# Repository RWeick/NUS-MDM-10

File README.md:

# NUS-MDM-10
The kicad schematic and pcb layout of the NUS-MDM-10 Nintendo 64DD modem cartridge

PCB Thickness: 1.2 mm

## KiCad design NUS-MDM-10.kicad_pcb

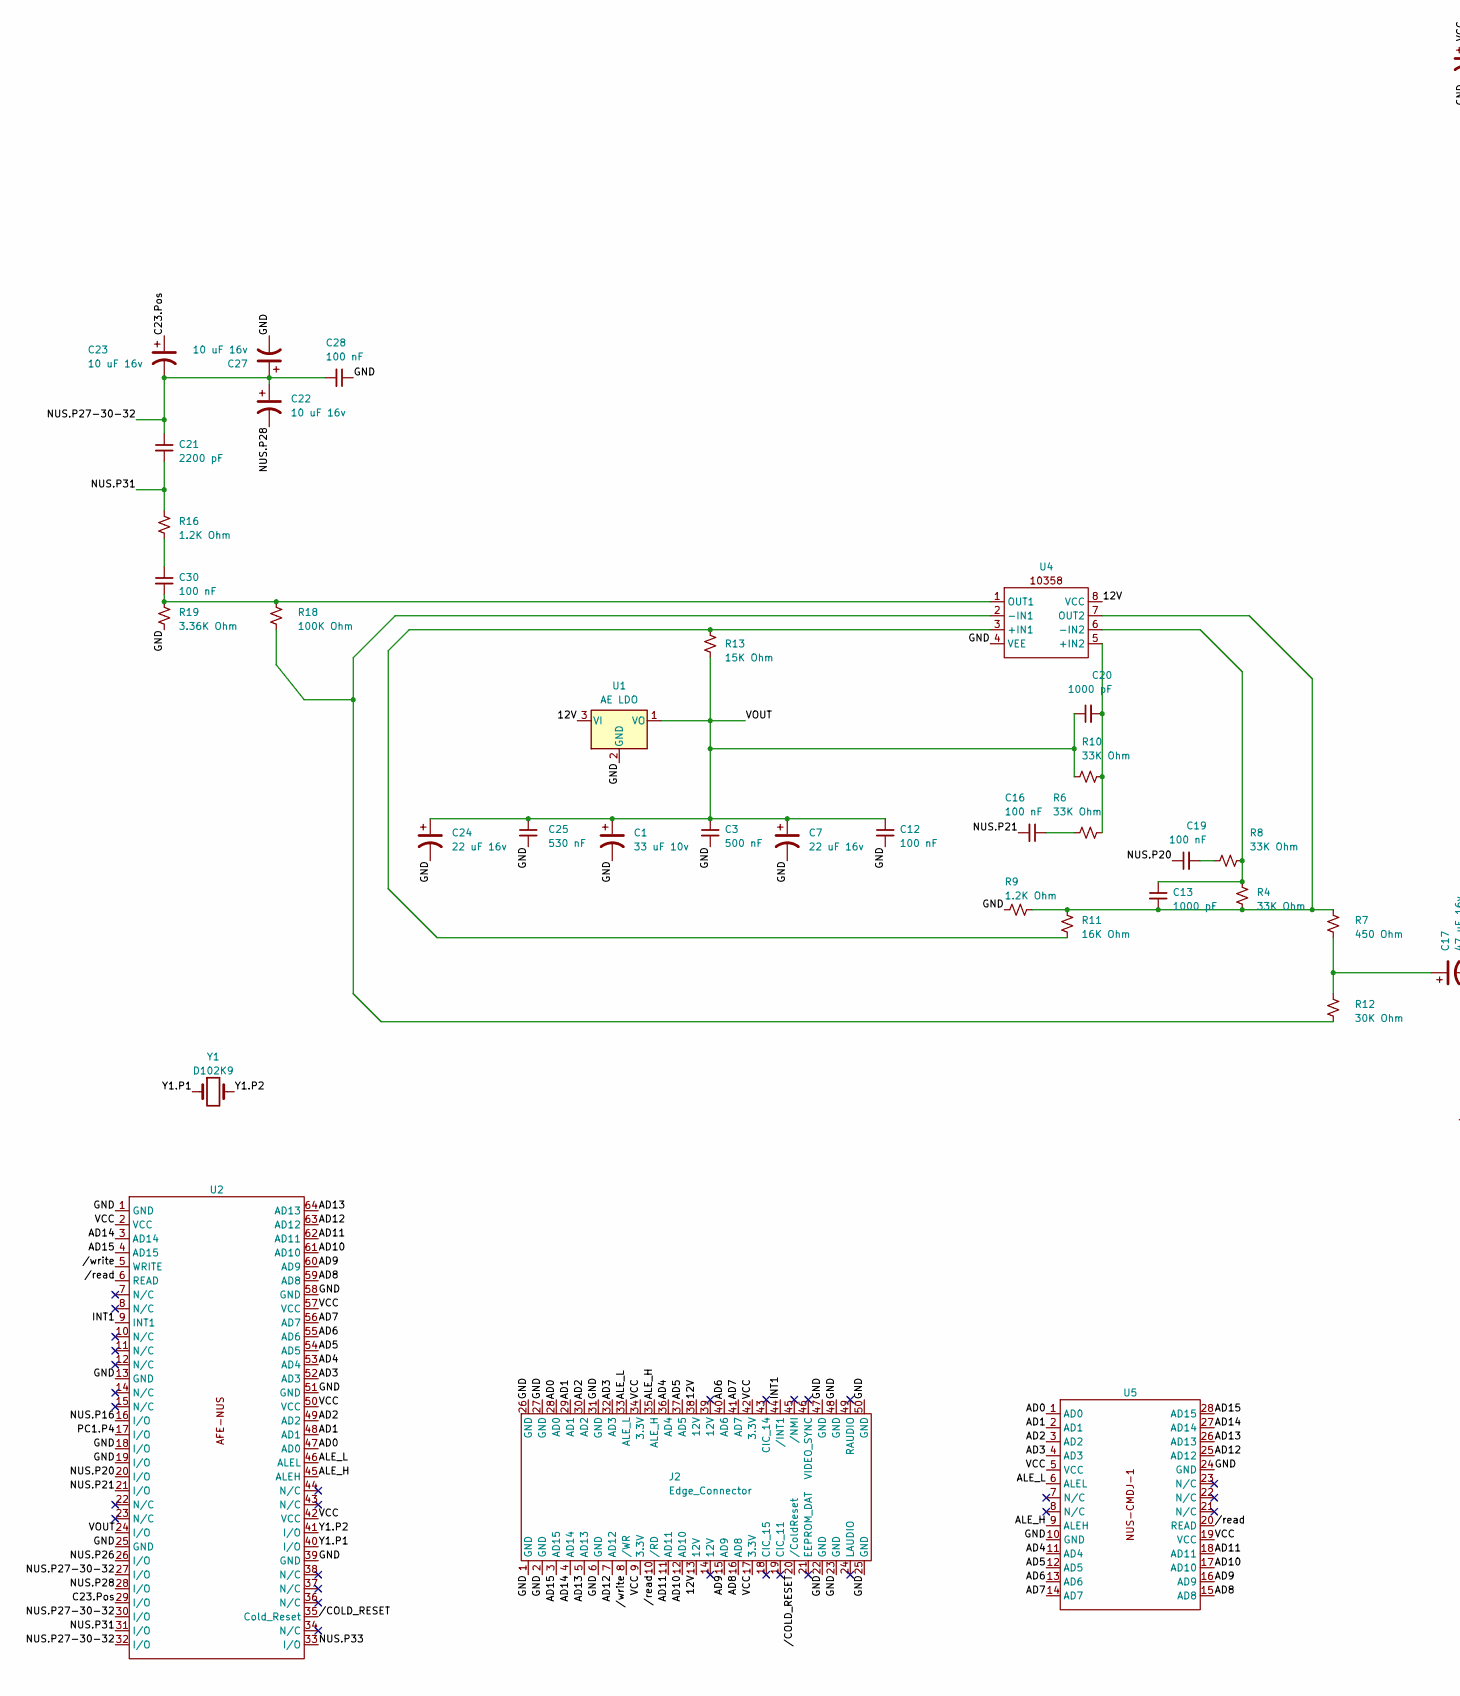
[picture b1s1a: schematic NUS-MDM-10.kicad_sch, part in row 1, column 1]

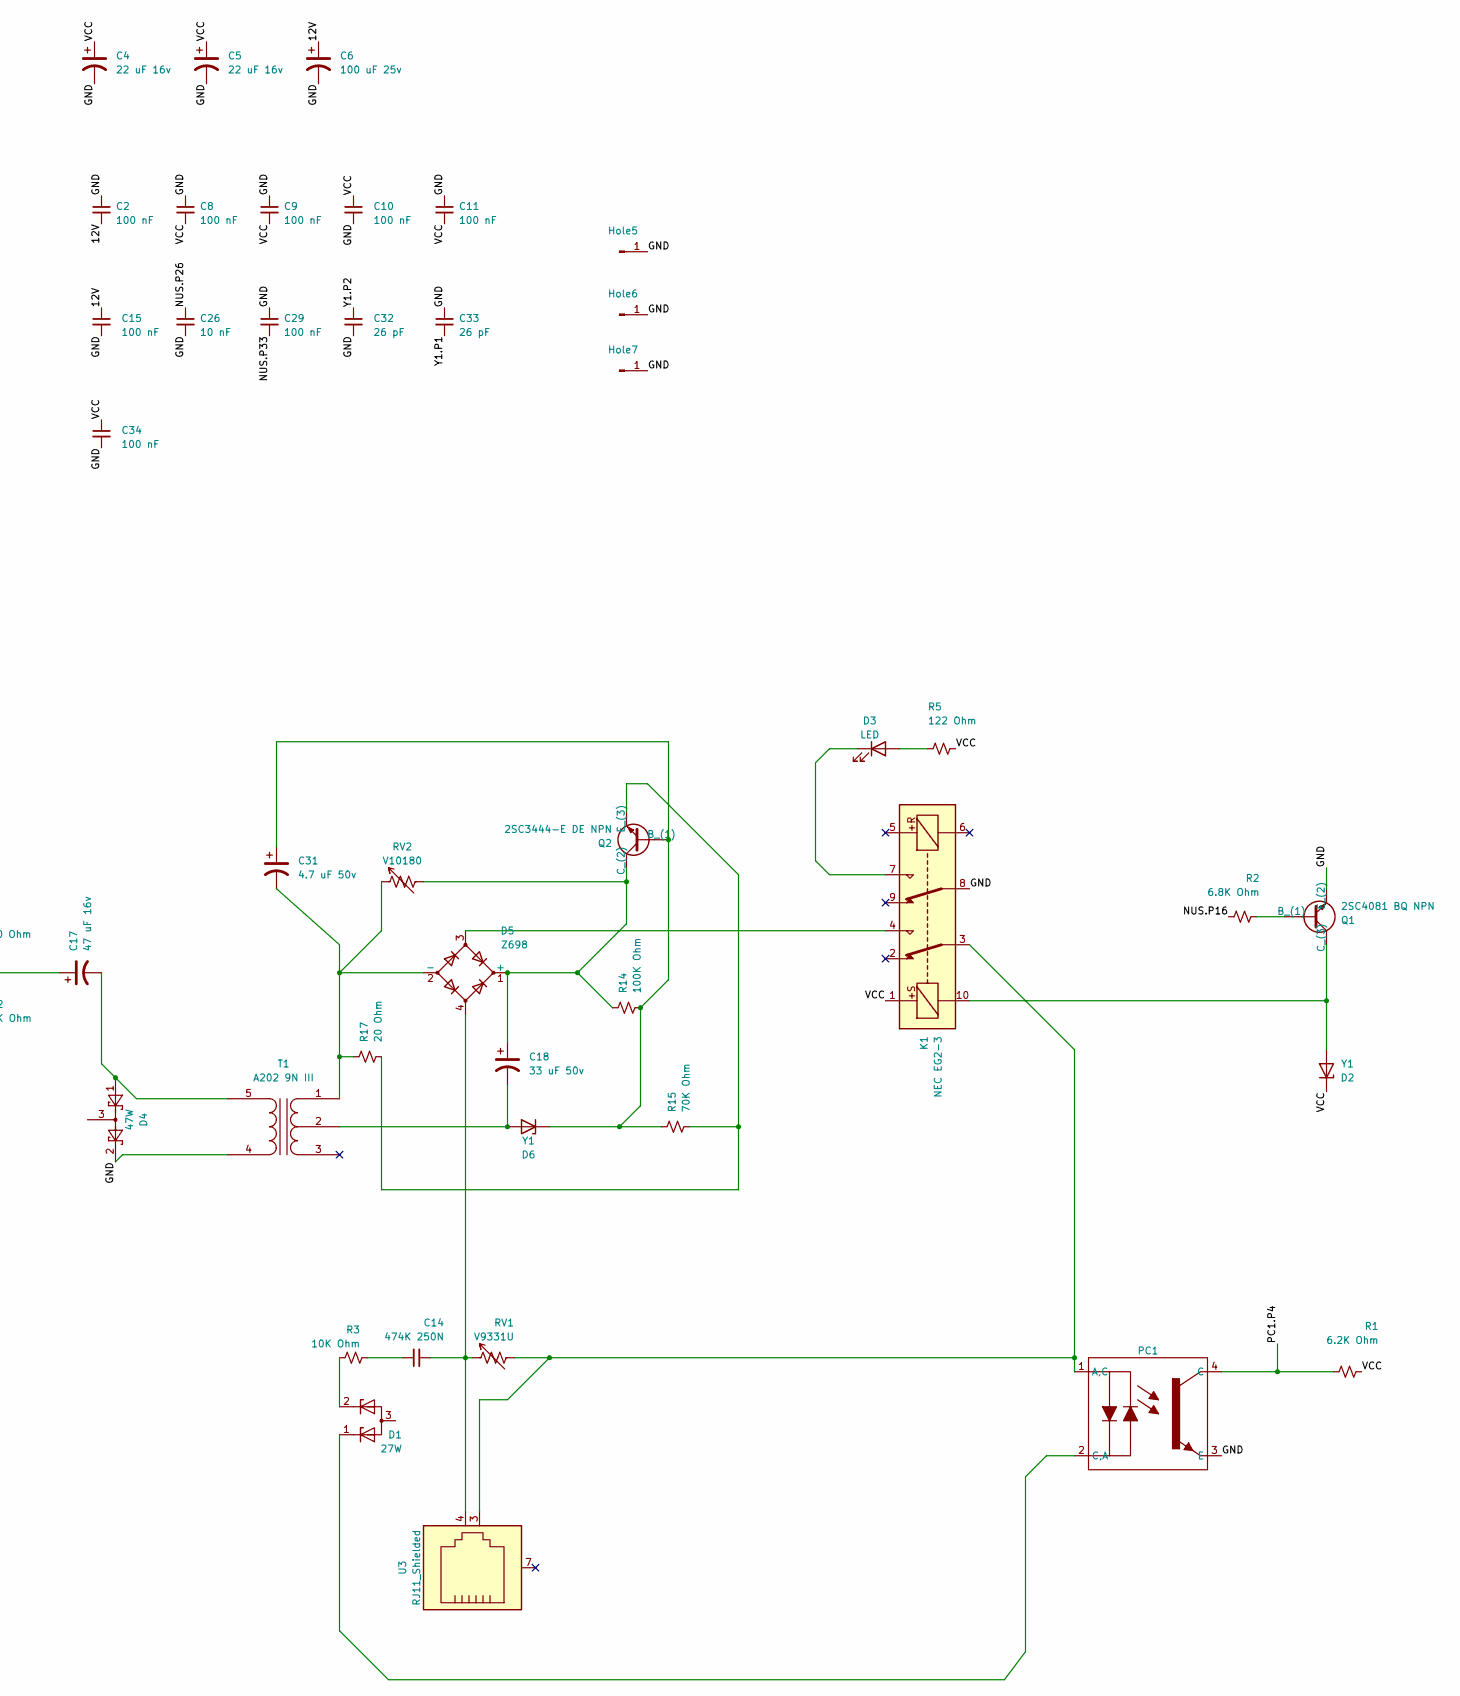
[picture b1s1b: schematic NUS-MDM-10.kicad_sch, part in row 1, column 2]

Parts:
C1: 33 uF 10v; C1
C2, C8, C9, C10, C11, C12, C15, C16, C19, C28, C29, C30, C34: 100 nF; SMD Cap Res
C3: 500 nF; SMD Cap Res
C4: 22 uF 16v; C4
C5: 22 uF 16v; C5
C6: 100 uF 25v; C6
C7: 22 uF 16v; C7
C13, C20: 1000 pF; SMD Cap Res
C14: 474K 250N; 474K Capacitor
C17: 47 uF 16v; C17
C18: 33 uF 50v; C18
C21: 2200 pF; SMD Cap Res
C22: 10 uF 16v; C22
C23: 10 uF 16v; C23
C24: 22 uF 16v; C24
C25: 530 nF; SMD Cap Res
C26: 10 nF; SMD Cap Res
C27: 10 uF 16v; C27
C31: 4.7 uF 50v; C31
C32, C33: 26 pF; SMD Cap Res
D1: 27W; D1
D2: Y1; D2
D3: LED
D4: 47W; D4
D5: Z698; 869Z
D6: Y1; D6
Hole5, Hole6, Hole7: Conn_01x01_Pin; Ground Panel Mounting Hole
J2: Edge_Connector; Cartridge Edge Connector
K1: NEC EG2-3
PC1: PC1
Q1: 2SC4081 BQ NPN; Q1
Q2: 2SC3444-E DE NPN; Q2
R1: 6.2K Ohm; SMD Cap Res
R2: 6.8K Ohm; SMD Cap Res
R3: 10K Ohm; SMD Cap Res
R4, R6, R8, R10: 33K Ohm; SMD Cap Res
R5: 122 Ohm; SMD Cap Res
R7: 450 Ohm; SMD Cap Res
R9, R16: 1.2K Ohm; SMD Cap Res
R11: 16K Ohm; SMD Cap Res
R12: 30K Ohm; SMD Cap Res
R13: 15K Ohm; SMD Cap Res
R14, R18: 100K Ohm; SMD Cap Res
R15: 70K Ohm; SMD Cap Res
R17: 20 Ohm; SMD Cap Res
R19: 3.36K Ohm; SMD Cap Res
RV1: V9331U
RV2: V10180
T1: A202 9N III; A202 Transformer
U1: AE LDO; U1
U2: AFE-NUS
U3: RJ11_Shielded; RJ11
U4: 10358
U5: NUS-CMDJ-1
Y1: D102K9

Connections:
/12V: C2.2, C6.1, C15.1, U1.3 (VI), U4.8 (VCC); also elsewhere on the board
/AD0: U2.47 (AD0), U5.1 (AD0); also elsewhere on the board
/AD1: U2.48 (AD1), U5.2 (AD1); also elsewhere on the board
/AD2: U2.49 (AD2), U5.3 (AD2); also elsewhere on the board
/AD3: U2.52 (AD3), U5.4 (AD3); also elsewhere on the board
/AD4: U2.53 (AD4), U5.11 (AD4); also elsewhere on the board
/AD5: U2.54 (AD5), U5.12 (AD5); also elsewhere on the board
/AD6: U2.55 (AD6), U5.13 (AD6); also elsewhere on the board
/AD7: U2.56 (AD7), U5.14 (AD7); also elsewhere on the board
/AD8: U2.59 (AD8), U5.15 (AD8); also elsewhere on the board
/AD9: U2.60 (AD9), U5.16 (AD9); also elsewhere on the board
/AD10: U2.61 (AD10), U5.17 (AD10); also elsewhere on the board
/AD11: U2.62 (AD11), U5.18 (AD11); also elsewhere on the board
/AD12: U2.63 (AD12), U5.25 (AD12); also elsewhere on the board
/AD13: U2.64 (AD13), U5.26 (AD13); also elsewhere on the board
/AD14: U2.3 (AD14), U5.27 (AD14); also elsewhere on the board
/AD15: U2.4 (AD15), U5.28 (AD15); also elsewhere on the board
/ALE_H: U2.45 (ALEH), U5.9 (ALEH); also elsewhere on the board
/ALE_L: U2.46 (ALEL), U5.6 (ALEL); also elsewhere on the board
/C23.Pos: C23.1, U2.29 (I/O)
/GND: C1.2, C2.1, C3.2, C4.2, C5.2, C6.2, C7.2, C8.1, C9.1, C10.2, C11.1, C12.2, C15.2, C24.2, C25.2, C26.2, C27.2, C28.1, C29.1, C32.2, C33.1, C34.2, D4.2, Hole5.1, Hole6.1, Hole7.1, K1.8, PC1.3 (E), Q1.2 (E_(2)), R9.2, R19.2, T1.4 (S1), U1.2 (GND), U2.1 (GND), U2.13 (GND), U2.18 (I/O), U2.19 (I/O), U2.25 (GND), U2.39 (GND), U2.51 (GND), U2.58 (GND), U4.4 (VEE), U5.10 (GND), U5.24 (GND); also elsewhere on the board
/INT1: U2.9 (INT1); also elsewhere on the board
/NUS.P16: R2.1, U2.16 (I/O)
/NUS.P20: C19.1, U2.20 (I/O)
/NUS.P21: C16.2, U2.21 (I/O)
/NUS.P26: C26.1, U2.26 (I/O)
/NUS.P27-30-32: C21.1, C22.1, C23.2, C27.1, C28.2, U2.27 (I/O), U2.30 (I/O), U2.32 (I/O)
/NUS.P28: C22.2, U2.28 (I/O)
/NUS.P31: C21.2, R16.1, U2.31 (I/O)
/NUS.P33: C29.2, U2.33 (I/O)
/PC1.P4: PC1.4 (C), R1.1, U2.17 (I/O)
/VCC: C4.1, C5.1, C8.2, C9.2, C10.1, C11.2, C34.1, D2.1 (K), K1.1, R1.2, R5.1, U2.2 (VCC), U2.42 (VCC), U2.50 (VCC), U2.57 (VCC), U5.19 (VCC); also elsewhere on the board
/VOUT: C1.1, C3.1, C7.1, C12.1, C20.1, C24.1, C25.1, R10.2, R13.2, U1.1 (VO), U2.24 (I/O)
/Y1.P1: C33.2, U2.40 (I/O), Y1.1
/Y1.P2: C32.1, U2.41 (I/O), Y1.2
//COLD_RESET: U2.35 (Cold_Reset); also elsewhere on the board
//read: U2.6 (READ), U5.20 (READ); also elsewhere on the board
//write: U2.5 (WRITE); also elsewhere on the board
unnamed: C14.1, R3.2
unnamed: C14.2, D5.4, RV1.1, U3.4
unnamed: C16.1, R6.1
unnamed: C17.1, R7.1, R12.2
unnamed: C19.2, R8.2
unnamed: C30.1, R16.2
unnamed: D1.2 (K), R3.1
unnamed: D2.2 (A), K1.10, Q1.3 (C_(3))
unnamed: D3.2 (A), R5.2
unnamed: D3.1 (K), K1.7
unnamed: C18.1, D5.1 (+), Q2.2 (C_(2)), R14.1, RV2.2
unnamed: C31.2, D5.2 (-), R17.1, RV2.1, T1.1 (PR1)
unnamed: D5.3, K1.4
unnamed: C18.2, D6.2 (A), T1.2 (PM)
unnamed: C31.1, D6.1 (K), Q2.1 (B_(1)), R14.2, R15.1
unnamed: K1.3, PC1.1 (A,C), RV1.2, U3.3
unnamed: D1.1 (K), PC1.2 (C,A)
unnamed: Q1.1 (B_(1)), R2.2
unnamed: Q2.3 (E_(3)), R15.2, R17.2
unnamed: C17.2, D4.1, T1.5 (S2)
unnamed: R11.1, R13.1, U4.3 (+IN1)
unnamed: C20.2, R6.2, R10.1, U4.5 (+IN2)
unnamed: R12.1, R18.1, U4.2 (-IN1)
unnamed: C13.1, R4.1, R8.1, U4.6 (-IN2)
unnamed: C30.2, R18.2, R19.1, U4.1 (OUT1)
unnamed: C13.2, R4.2, R7.2, R9.1, R11.2, U4.7 (OUT2)

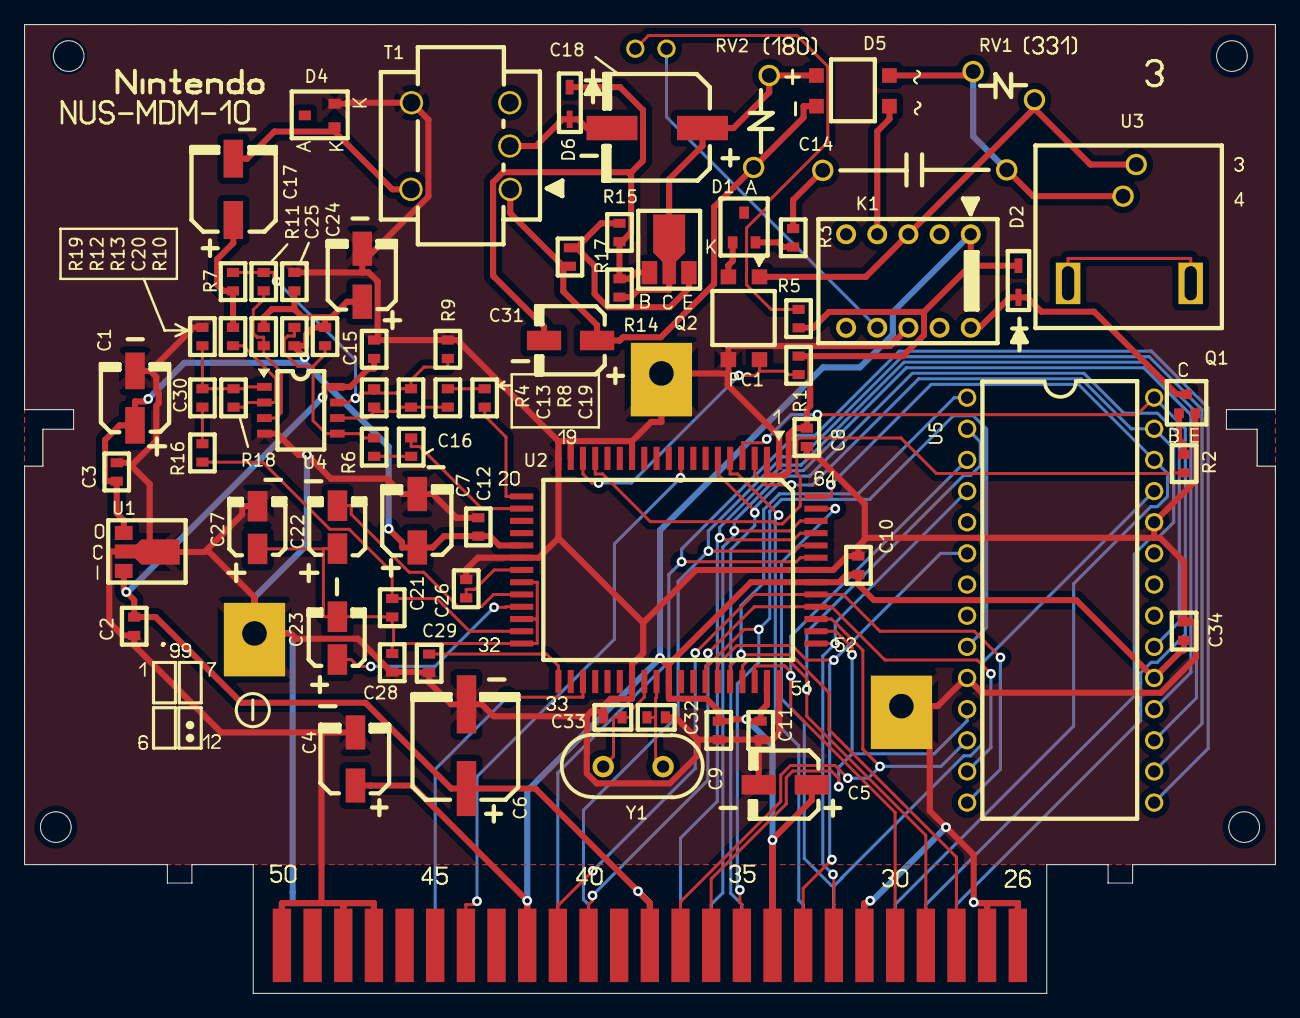
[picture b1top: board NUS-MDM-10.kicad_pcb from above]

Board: 2 copper layers, 102.0 x 79.0 mm, 80 parts (0 on the bottom side), 64 nets.

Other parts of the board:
Hole1, Hole2, Hole3, Hole4: MountingHole_2.5mm
J1: Edge_Connector; Cartridge Edge Connector

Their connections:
/12V: J1.13 (12V), J1.38 (12V); also elsewhere on the board
/AD0: J1.28 (AD0); also elsewhere on the board
/AD1: J1.29 (AD1); also elsewhere on the board
/AD2: J1.30 (AD2); also elsewhere on the board
/AD3: J1.32 (AD3); also elsewhere on the board
/AD4: J1.36 (AD4); also elsewhere on the board
/AD5: J1.37 (AD5); also elsewhere on the board
/AD6: J1.40 (AD6); also elsewhere on the board
/AD7: J1.41 (AD7); also elsewhere on the board
/AD8: J1.16 (AD8); also elsewhere on the board
/AD9: J1.15 (AD9); also elsewhere on the board
/AD10: J1.12 (AD10); also elsewhere on the board
/AD11: J1.11 (AD11); also elsewhere on the board
/AD12: J1.7 (AD12); also elsewhere on the board
/AD13: J1.5 (AD13); also elsewhere on the board
/AD14: J1.4 (AD14); also elsewhere on the board
/AD15: J1.3 (AD15); also elsewhere on the board
/ALE_H: J1.35 (ALE_H); also elsewhere on the board
/ALE_L: J1.33 (ALE_L); also elsewhere on the board
/GND: J1.1 (GND), J1.2 (GND), J1.6 (GND), J1.22 (GND), J1.23 (GND), J1.25 (GND), J1.26 (GND), J1.27 (GND), J1.31 (GND), J1.47 (GND), J1.48 (GND), J1.50 (GND); also elsewhere on the board
/INT1: J1.44 (/INT1); also elsewhere on the board
/VCC: J1.9 (3.3V), J1.17 (3.3V), J1.34 (3.3V), J1.42 (3.3V); also elsewhere on the board
//COLD_RESET: J1.20 (/ColdReset); also elsewhere on the board
//read: J1.10 (/RD); also elsewhere on the board
//write: J1.8 (/WR); also elsewhere on the board
